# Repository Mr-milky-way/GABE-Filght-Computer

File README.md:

# G.A.B.E.-Filght-Computer
*Good Avionics, Bad Engineer*

## What is it?
The GABE flight computer is an open source rocket flight computer for controlling amateur or model rockets. It's a 4 layer PCB and pretty standard. It has a CoCom locked GPS, and 2 IMUs, a BMP390, 8 different servo header pins and can be powered off of a 12-26v battery. It uses and arm switch to power it on and has 6 pyro channels. It uses the MIMXRT1062DVJ6B with a teensy bootloader.

I tried to make it look nice but IDK, also that cad needs some work so thats why it's not shown.

> [!NOTE]
> The code is a demo of the Servos, LED, Pyros, and buzzer. This is so I have A low or very low ITAR risk. :)

## Why?
For aboout 3 years at this point I have wanted to make a Fin controlled rocket, and my first flight computter was, well a first. It didn't work really well and ended up frying itself via the servo PWM lines (I fixed that on this one with a level shifter). It was also large and bulky and the wire connectors were to small, not to mention it was ugly. So I set out to make this one.
I wanted it to look nice and work well and use mostly SMD parts, and for the most part I did.

## PICTURES

## BOM
Some parts have a value different from what it should be, this is because it was only one I could find. :)

| Part                             | Cost (all parts) | Count | Supplyer | Link                                                                                                                                                                                                                                                                          | Part ID                                     | Use              | Value         |
| -------------------------------- | ---------------- | ----- | -------- | ----------------------------------------------------------------------------------------------------------------------------------------------------------------------------------------------------------------------------------------------------------------------------- | ------------------------------------------- | ---------------- | ------------- |
| MIMXRT1062DVJ6B                  | $11.93           | 1     | Digikey  | [MIMXRT1062DVJ6B NXP USA Inc. \| Integrated Circuits (ICs) \| DigiKey](https://www.digikey.com/en/products/detail/nxp-usa-inc/MIMXRT1062DVJ6B/13574426)                                                                                                                       | U5                                          | MPU              |               |
| BNO055                           | $12.34           | 1     | Digikey  | [BNO055 Bosch Sensortec \| Sensors, Transducers \| DigiKey](https://www.digikey.com/en/products/detail/bosch-sensortec/BNO055/6136301)                                                                                                                                        | U1                                          | IMU              |               |
| TXB0108PWRG4                     | $1.41            | 1     | Digikey  | [TXB0108PWRG4 Texas Instruments \| Integrated Circuits (ICs) \| DigiKey](https://www.digikey.com/en/products/detail/texas-instruments/TXB0108PWRG4/1910158)                                                                                                                   | U6                                          | Level Shifter    |               |
| RTAN0805BKE10K0                  | $0.34            | 1     | Digikey  | [RTAN0805BKE10K0 Stackpole Electronics Inc \| Resistors \| DigiKey](https://www.digikey.com/en/products/detail/stackpole-electronics-inc/RTAN0805BKE10K0/6602188)                                                                                                             | R1                                          | Resistor         | 10KΩ          |
| FC-135R 32.7680KF-A0             | $2.13            | 3     | Digikey  | [FC-135R 32.7680KF-A0 EPSON \| Crystals, Oscillators, Resonators \| DigiKey](https://www.digikey.com/en/products/detail/epson/FC-135R-32-7680KF-A0/5604247)                                                                                                                   | X1,X2,X4                                    | Crystal          | 32.7680KHZ    |
| CHV0805N250220FCT                | $2.12            | 4     | Digikey  | [CHV0805N250220FCT Cal-Chip Electronics, Inc. \| Capacitors \| DigiKey](https://www.digikey.com/en/products/detail/cal-chip-electronics-inc/CHV0805N250220FCT/22155267)                                                                                                       | C1,C2,C5,C6                                 | Capacitor        | 22PF          |
| CC0805KRX7R9BB104                | $0.48            | 6     | Digikey  | [CC0805KRX7R9BB104 YAGEO \| Capacitors \| DigiKey](https://www.digikey.com/en/products/detail/yageo/CC0805KRX7R9BB104/302874)                                                                                                                                                 | C3,C4,C7,C8,C11,C12                         | Capacitor        | 0.1UF         |
| BNO085                           | $13.05           | 1     | Digikey  | [BNO085 CEVA Technologies, Inc. \| Sensors, Transducers \| DigiKey](https://www.digikey.com/en/products/detail/ceva-technologies-inc/BNO085/9445940)                                                                                                                          | U2                                          | IMU              |               |
| BMP390                           | $3.15            | 1     | Digikey  | [BMP390 Bosch Sensortec \| Sensors, Transducers \| DigiKey](https://www.digikey.com/en/products/detail/bosch-sensortec/BMP390/16164575)                                                                                                                                       | U3                                          |                  |               |
| NEO-M9N-00B                      | $27.00           | 1     | Digikey  | [NEO-M9N-00B u-blox \| RF and Wireless \| DigiKey](https://www.digikey.com/en/products/detail/u-blox/NEO-M9N-00B/12149174)                                                                                                                                                    | U4                                          | GPS              |               |
| CONSMA001-C-G                    | $2.79            | 1     | Digikey  | [CONSMA001-C-G TE Connectivity Linx \| Connectors, Interconnects \| DigiKey](https://www.digikey.com/en/products/detail/te-connectivity-linx/CONSMA001-C-G/11482824)                                                                                                          | X3                                          | SMA connector    |               |
| RG0603R-330-D-T10                | $0.16            | 1     | Digikey  | [RG0603R-330-D-T10 Susumu \| Resistors \| DigiKey](https://www.digikey.com/en/products/detail/susumu/RG0603R-330-D-T10/18103232)                                                                                                                                              | R2                                          | Resistor         | 33Ω           |
| BLM15PX121SN1D                   | $0.30            | 3     | Digikey  | [BLM15PX121SN1D Murata Electronics \| Filters \| DigiKey](https://www.digikey.com/en/products/detail/murata-electronics/BLM15PX121SN1D/4421095)                                                                                                                               | FB1-FB3                                     | Ferrite Bead     | 120Ω          |
| CC0805JRNPO9BN470                | $0.10            | 1     | Digikey  | [CC0805JRNPO9BN470 YAGEO \| Capacitors \| DigiKey](https://www.digikey.com/en/products/detail/yageo/CC0805JRNPO9BN470/302841)                                                                                                                                                 | C9                                          | Capacitor        | 47PF          |
| ML414H IV01E                     | $1.84            | 1     | Digikey  | [ML414H IV01E Seiko Instruments \| Battery Products \| DigiKey](https://www.digikey.com/en/products/detail/seiko-instruments/ML414H-IV01E/1889203)                                                                                                                            | BT1                                         | Battery Holder   |               |
| PMEG4005AEA-QX                   | $0.32            | 1     | Digikey  | [https://www.digikey.com/en/products/detail/nexperia-usa-inc/PMEG4005AEA-QX/17295512](https://www.digikey.com/en/products/detail/nexperia-usa-inc/PMEG4005AEA-QX/17295512)                                                                                                    | D1                                          | Diode            |               |
| RG0603P-102-B-T10                | $0.20            | 1     | Digikey  | [RG0603P-102-B-T10 Susumu \| Resistors \| DigiKey](https://www.digikey.com/en/products/detail/susumu/RG0603P-102-B-T10/18103206)                                                                                                                                              | R3                                          | Resistor         | 1KΩ           |
| C0805C105K9RACTU                 | $0.15            | 1     | Digikey  | [C0805C105K9RACTU KEMET \| Capacitors \| DigiKey](https://www.digikey.com/en/products/detail/kemet/C0805C105K9RACTU/2211772)                                                                                                                                                  | C10                                         | Capacitor        | 1UF           |
| BL-HBXJXGX32L                    | $0.50            | 1     | Digikey  | [BL-HBXJXGX32L American Bright Optoelectronics Corporation](https://www.digikey.com/en/products/detail/american-bright-optoelectronics-corporation/BL-HBXJXGX32L/9678124)                                                                                                     | D2                                          | LED              |               |
| XRCGB24M000F3M00R0               | $0.30            | 1     | Digikey  | [XRCGB24M000F3M00R0 Murata Electronics \| Crystals, Oscillators, Resonators \| DigiKey](https://www.digikey.com/en/products/detail/murata-electronics/XRCGB24M000F3M00R0/2368376) | Y1                                          | Crystal          | 24MHZ         |
| MLZ2012N4R7LT000                 | $0.10            | 1     | Digikey  | [MLZ2012N4R7LT000 TDK Corporation \| Inductors, Coils, Chokes \| DigiKey](https://www.digikey.com/en/products/detail/tdk-corporation/MLZ2012N4R7LT000/2523498)                                                                                                                | L1                                          | Inductor         | 4.7UH         |
| 112J-TDAR-R01                    | $2.52            | 1     | Digikey  | [112J-TDAR-R01 ATTEND Technology \| Connectors, Interconnects \| DigiKey](https://www.digikey.com/en/products/detail/attend-technology/112J-TDAR-R01/17633874)                                                                                                                | K1                                          | SD card holder   |               |
| BAT54CTB6_R1_00001               | $0.25            | 1     | Digikey  | [BAT54CTB6_R1_00001 Panjit International Inc. \| Discrete Semiconductor Products \| DigiKey](https://www.digikey.com/en/products/detail/panjit-international-inc/BAT54CTB6-R1-00001/15796775)                                                                                 | U$1                                         | Diode            |               |
| SKRPACE010                       | $0.21            | 1     | Digikey  | [SKRPACE010 Alps Alpine \| Switches \| DigiKey](https://www.digikey.com/en/products/detail/alps-alpine/SKRPACE010/18115579)                                                                                                                                                   | S1                                          | Switch           |               |
| W25Q64JVXGIM                     | $1.20            | 1     | PJRC     | [Bootloader Chip for DIY Teensy 4.0 & 4.1 Projects](https://www.pjrc.com/store/ic_mkl02_t4.html)                                                                                                                                                                              | U9                                          | Flash Chip       |               |
| MKL02Z32                         | $6.25            | 1     | PJRC     | [Bootloader Chip for DIY Teensy 4.0 & 4.1 Projects](https://www.pjrc.com/store/ic_mkl02_t4.html)                                                                                                                                                                              | U8                                          | Bootloader       |               |
| W25N01GVZEIG TR                  | $3.01            | 1     | Digikey  | [W25N01GVZEIG TR Winbond Electronics \| Integrated Circuits (ICs) \| DigiKey](https://www.digikey.com/en/products/detail/winbond-electronics/W25N01GVZEIG-TR/5803931)                                                                                                         | U10                                         | Flash Chip       |               |
| SMTB-1240-S-R                    | $1.35            | 1     | Digikey  | [SMTB-1240-S-R PUI Audio, Inc. \| Audio Products \| DigiKey](https://www.digikey.com/en/products/detail/pui-audio-inc/SMTB-1240-S-R/13165906)                                                                                                                                 | LS1                                         | Buzzer           |               |
| IRLML6344TRPBF                   | $2.10            | 6     | Digikey  | [IRLML6344TRPBF Infineon Technologies \| Discrete Semiconductor Products \| DigiKey](https://www.digikey.com/en/products/detail/infineon-technologies/IRLML6344TRPBF/2538152)                                                                                                 | Q2-Q7                                       | Mosfet           |               |
| LM7805MPX/NOPB                   | $1.38            | 1     | Digikey  | [LM7805MPX/NOPB Texas Instruments \| Integrated Circuits (ICs) \| DigiKey](https://www.digikey.com/en/products/detail/texas-instruments/LM7805MPX-NOPB/6110583)                                                                                                               | VR1                                         | Voltage Reguator |               |
| TLV75533PDBVR                    | $0.32            | 1     | Digikey  | [TLV75533PDBVR Texas Instruments \| Integrated Circuits (ICs) \| DigiKey](https://www.digikey.com/en/products/detail/texas-instruments/TLV75533PDBVR/9356541)                                                                                                                 | U7                                          | Voltage Reguator |               |
| AK100/2DS-5.0-V-GREY             | $5.64            | 12    | Digikey  | [https://www.digikey.com/en/products/detail/ptr-hartmann/AK100-2DS-5-0-V-GREY/24787150](https://www.digikey.com/en/products/detail/ptr-hartmann/AK100-2DS-5-0-V-GREY/24787150)                                                                                                | U$2-U$13                                    | Terminal Block   |               |
| GCJ21BL8YA224KA01L               | $3.52            | 11    | Digikey  | [GCJ21BL8YA224KA01L Murata Electronics \| Capacitors \| DigiKey](https://www.digikey.com/en/products/detail/murata-electronics/GCJ21BL8YA224KA01L/11618469)                                                                                                                   | C13,C14,C17,C18,C20,C23,C26,C31,C33,C34,C36 | Capacitor        | .22UF         |
| C0805C200J3HACAUTO               | $0.26            | 2     | Digikey  | [C0805C200J3HACAUTO KEMET \| Capacitors \| DigiKey](https://www.digikey.com/en/products/detail/kemet/C0805C200J3HACAUTO/7958823)                                                                                                                                              | C15,C16                                     | Capacitor        | 20PF          |
| GRM21BR61H475KE51L               | $0.95            | 5     | Digikey  | [GRM21BR61H475KE51L Murata Electronics \| Capacitors \| DigiKey](https://www.digikey.com/en/products/detail/murata-electronics/GRM21BR61H475KE51L/4905540)                                                                                                                    | C19,C21,C24,C27,C30                         | Capacitor        | 4.7UF         |
| CGA4J1X7R1V225K125AC             | $0.46            | 1     | Digikey  | [CGA4J1X7R1V225K125AC TDK Corporation \| Capacitors \| DigiKey](https://www.digikey.com/en/products/detail/tdk-corporation/CGA4J1X7R1V225K125AC/2672856)                                                                                                                      | C25                                         | Capacitor        | 2.2UF         |
| CC0805KRX7R8BB103                | $0.10            | 1     | Digikey  | [CC0805KRX7R8BB103 YAGEO \| Capacitors \| DigiKey](https://www.digikey.com/en/products/detail/yageo/CC0805KRX7R8BB103/5884212)                                                                                                                                                | C22                                         | Capacitor        | 10NF          |
| GRM21BR6YA106KE43L               | $1.36            | 4     | Digikey  | [GRM21BR6YA106KE43L Murata Electronics \| Capacitors \| DigiKey](https://www.digikey.com/en/products/detail/murata-electronics/GRM21BR6YA106KE43L/5027598)                                                                                                                    | C28,C29,C32,C35                             | Capacitor        | 10UF          |
| C0805C120J3GACTU                 | $0.44            | 2     | Digikey  | [C0805C120J3GACTU KEMET \| Capacitors \| DigiKey](https://www.digikey.com/en/products/detail/kemet/C0805C120J3GACTU/7388391)                                                                                                                                                  | C37,C38                                     | Capacitor        | 12pF          |
| UJ2-MIBH-G-SMT-TR                | $0.44            | 1     | Digikey  | [UJ2-MIBH-G-SMT-TR Same Sky (Formerly CUI Devices) \| Connectors, Interconnects \| DigiKey](https://www.digikey.com/en/products/detail/same-sky-formerly-cui-devices/UJ2-MIBH-G-SMT-TR/13680627)                                                                              | J1                                          | USB Con          |               |
| B4B-XH-A                         | $0.17            | 1     | Digikey  | [B4B-XH-A JST Sales America Inc. \| Connectors, Interconnects \| DigiKey](https://www.digikey.com/en/products/detail/jst-sales-america-inc/B4B-XH-A/1651047)                                                                                                                  | J2                                          | JST Con          |               |
| 61300311121                      | $0.96            | 8     | Digikey  | https://www.digikey.com/en/products/detail/würth-elektronik/61300311121/4846825                                                                                                                                                                                               | M1-M8                                       | Header pins      |               |
| DMG2305UX-7                      | $0.18            | 1     | Digikey  | [DMG2305UX-7 Diodes Incorporated \| Discrete Semiconductor Products \| DigiKey](https://www.digikey.com/en/products/detail/diodes-incorporated/DMG2305UX-7/4340667)                                                                                                           | Q1                                          | Mosfet           |               |
| SDR10EZPF2201                    | $0.44            | 2     | Digikey  | [SDR10EZPF2201 Rohm Semiconductor \| Resistors \| DigiKey](https://www.digikey.com/en/products/detail/rohm-semiconductor/SDR10EZPF2201/16179905)                                                                                                                              | R4,R5                                       | Resistor         | 2.2kΩ         |
| SDR10EZPF1003                    | $0.44            | 2     | Digikey  | [SDR10EZPF1003 Rohm Semiconductor \| Resistors \| DigiKey](https://www.digikey.com/en/products/detail/rohm-semiconductor/SDR10EZPF1003/17140208)                                                                                                                              | R6,R7                                       | Resistor         | 100kΩ         |
| SDR10EZPF2204                    | $0.22            | 1     | Digikey  | [SDR10EZPF2204 Rohm Semiconductor \| Resistors \| DigiKey](https://www.digikey.com/en/products/detail/rohm-semiconductor/SDR10EZPF2204/19531048)                                                                                                                              | R8                                          | Resistor         | 2.2MΩ         |
| SDR10EZPF1R00                    | $1.54            | 7     | Digikey  | [SDR10EZPF1R00 Rohm Semiconductor \| Resistors \| DigiKey](https://www.digikey.com/en/products/detail/rohm-semiconductor/SDR10EZPF1R00/16179859)                                                                                                                              | R9,R13,R15,R17,R19,R21,R23                  | Resistor         | 1Ω            |
| RLT1220-F-5R00-FNH               | $0.47            | 1     | Digikey  | [RLT1220-F-5R00-FNH Delta Electronics/Cyntec \| Resistors \| DigiKey](https://www.digikey.com/en/products/detail/delta-electronics-cyntec/RLT1220-F-5R00-FNH/9762198)                                                                                                         | R10                                         | Resistor         | 5Ω            |
| RK73H2ATTD64R9F                  | $0.10            | 1     | Digikey  | [RK73H2ATTD64R9F KOA Speer Electronics, Inc. \| Resistors \| DigiKey](https://www.digikey.com/en/products/detail/koa-speer-electronics-inc/RK73H2ATTD64R9F/10228485?)                                                                                                         | R11                                         | Resistor         | 65Ω (64.9)    |
| SDR10EZPF4700                    | $1.32            | 6     | Digikey  | [SDR10EZPF4700 Rohm Semiconductor \| Resistors \| DigiKey](https://www.digikey.com/en/products/detail/rohm-semiconductor/SDR10EZPF4700/17140152)                                                                                                                              | R12,R14,R16,R18,R20,R22                     | Resistor         | 470Ω          |
| RT0805BRD07723RL                 | $0.17            | 1     | Digikey  | [RT0805BRD07723RL YAGEO \| Resistors \| DigiKey](https://www.digikey.com/en/products/detail/yageo/RT0805BRD07723RL/7708570)                                                                                                                                                   | R24                                         | Resistor         | 722Ω (723)    |
| RK73H2ATTD1691F                  | $0.10            | 1     | Digikey  | [RK73H2ATTD1691F KOA Speer Electronics, Inc. \| Resistors \| DigiKey](https://www.digikey.com/en/products/detail/koa-speer-electronics-inc/RK73H2ATTD1691F/10234184)                                                                                                          | R25                                         | Resistor         | 1700Ω (1.69k) |
| COST OF MAIN PCB AND SMD-Stencil | $81.42           | 1     | PCB Way  |                                                                                                                                                                                                                                                                               |                                             | PCB              |               |
| TOTAL                            | $200.00          | 120   |          |                                                                                                                                                                                                                                                                               |                                             |                  |               |

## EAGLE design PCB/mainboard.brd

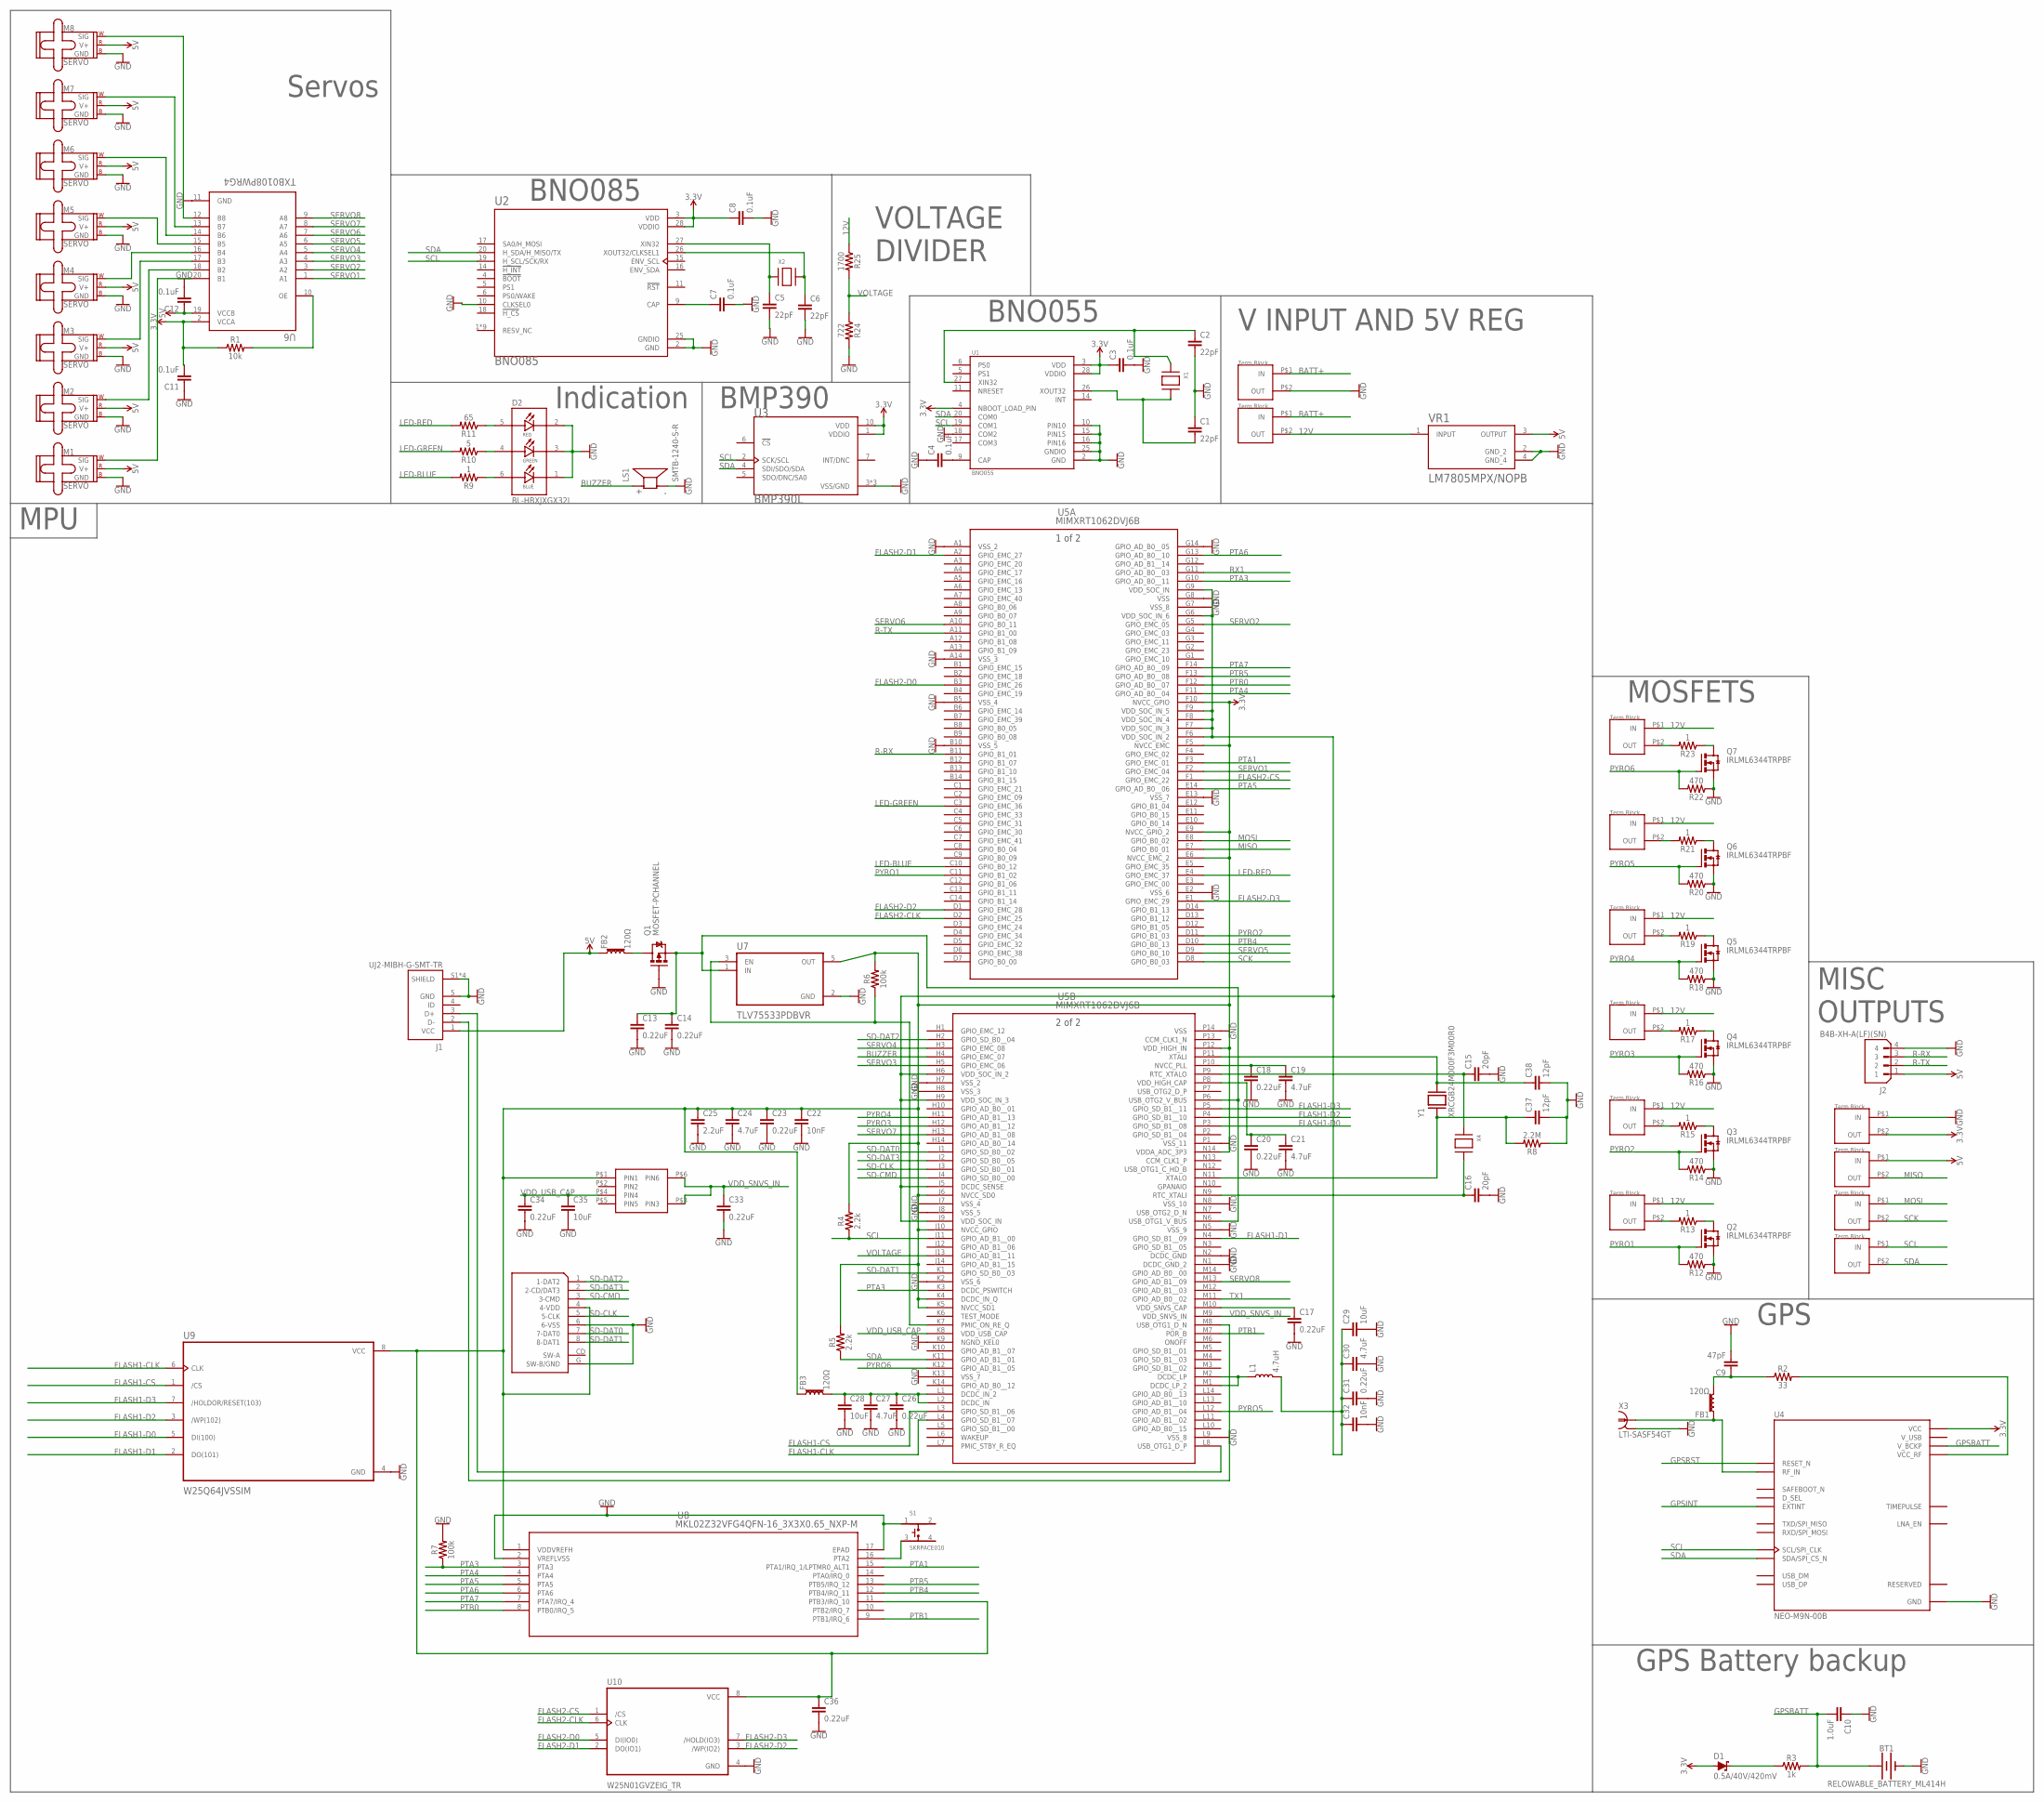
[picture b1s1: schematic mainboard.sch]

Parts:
BT1: RELOWABLE_BATTERY_ML414H; ML414H_IV01E
C1, C2, C5, C6: 22pF; 0805
C3, C4, C7, C8, C11, C12: 0.1uF; 0805
C9: 47pF; 0805
C10: 1.0uF; 0805
C13, C14, C17, C18, C20, C23, C26, C31, C33, C34, C36: 0.22uF; 0805
C15, C16: 20pF; 0805
C19, C21, C24, C27, C30: 4.7uF; 0805
C22, C32: 10nF; 0805
C25: 2.2uF; 0805
C28, C29, C35: 10uF; 0805
C37, C38: 12pF; 0805
D1: 0.5A/40V/420mV; SOD-323
D2: BL-HBXJXGX32L; LED_BL-HBXJXGX32L
FB1, FB2, FB3: 120Ω; 0805
J1: UJ2-MIBH-G-SMT-TR; CUI_UJ2-MIBH-G-SMT-TR
J2: B4B-XH-A(LF)(SN); JST_B4B-XH-A(LF)(SN)
K1: 112J-TDAR-R01
L1: 4.7uH; 0805-WIDE
LS1: SMTB-1240-S-R; XDCR_SMTB-1240-S-R
M1, M2, M3, M4, M5, M6, M7, M8: SERVO; 1X03
Q1: MOSFET-PCHANNEL; SOT23-3
Q2, Q3, Q4, Q5, Q6, Q7: IRLML6344TRPBF; SOT23
R1: 10k; 0805
R2: 33; 0805
R3: 1k; 0805
R4, R5: 2.2k; 0805
R6, R7: 100k; 0805
R8: 2.2M; 0805
R9, R13, R15, R17, R19, R21, R23: 1; 0805
R10: 5; 0805
R11: 65; 0805
R12, R14, R16, R18, R20, R22: 470; 0805
R24: 722; 0805
R25: 1700; 0805
S1: SKRPACE010; SW_SKRPACE010
U1: BNO055; LGA28R50P4X10_380X520X100
U2: BNO085; IC_BNO085
U3: BMP390L; XDCR_BMP390L
U4: NEO-M9N-00B; XCVR_NEO-M9N-00B
U5: MIMXRT1062DVJ6B; BGA196_MIMXRT_NXP
U6: TXB0108PWRG4; SOP65P640X120-20N
U7: TLV75533PDBVR; SOT95P280X145-5N
U8: MKL02Z32VFG4QFN-16_3X3X0.65_NXP-M; QFN-16_3X3X0.65_NXP-M
U9: W25Q64JVSSIM; SOIC127P790X216-8N
U10: W25N01GVZEIG_TR; SON127P800X600X80-9N
U$1: BAT54CTB6
U$2, U$3, U$4, U$5, U$6, U$7, U$8, U$9, U$10, U$11, U$12, U$13: AK100
VR1: LM7805MPX/NOPB; VREG_LM7805MPX/NOPB
X1, X2, X4: XTAL-3.2X1.5; XTAL3215
X3: LTI-SASF54GT
Y1: XRCGB24M000F3M00R0; OSC_XRCGB24M000F3M00R0

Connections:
3.3V: C3.1, C8.1, C11.2, C22.1, C23.1, C24.1, C25.1, C36.1, D1.A, FB3.1, K1.4 (4-VDD), R1.1, R4.2, R5.2, R6.2, U1.3 (VDD), U1.4 (NBOOT_LOAD_PIN), U1.28 (VDDIO), U2.3 (VDD), U2.28 (VDDIO), U3.1 (VDDIO), U3.10 (VDD), U4.23 (VCC), U5.E6 (NVCC_EMC_2), U5.E9 (NVCC_GPIO_2), U5.F5 (NVCC_EMC), U5.F10 (NVCC_GPIO), U5.J6 (NVCC_SD0), U5.J10 (NVCC_GPIO), U5.K4 (DCDC_IN_Q), U5.K5 (NVCC_SD1), U5.N14 (VDDA_ADC_3P3), U5.P12 (VDD_HIGH_IN), U6.2 (VCCA), U7.5 (OUT), U8.1 (VDDVREFH), U8.11 (PTB3/IRQ_10), U9.8 (VCC), U10.8 (VCC), U$1.P$1 (PIN1), U$11.P$2 (OUT)
5V: C12.1, FB2.1, J1.1 (VCC), J2.1, M1.2 (V+), M2.2 (V+), M3.2 (V+), M4.2 (V+), M5.2 (V+), M6.2 (V+), M7.2 (V+), M8.2 (V+), U6.19 (VCCB), U$10.P$1 (IN), VR1.3 (OUTPUT)
12V: R25.1, U$2.P$1 (IN), U$3.P$1 (IN), U$4.P$1 (IN), U$5.P$1 (IN), U$6.P$1 (IN), U$8.P$1 (IN), U$13.P$2 (OUT), VR1.1 (INPUT)
BATT+: U$12.P$1 (IN), U$13.P$1 (IN)
BUZZER: LS1.P (+), U5.H4 (GPIO_EMC_07)
FLASH1-CLK: U5.L4 (GPIO_SD_B1__07), U9.6 (CLK)
FLASH1-CS: U5.L3 (GPIO_SD_B1__06), U9.1 (/CS)
FLASH1-D0: U5.P3 (GPIO_SD_B1__08), U9.5 (DI(100))
FLASH1-D1: U5.N4 (GPIO_SD_B1__09), U9.2 (DO(101))
FLASH1-D2: U5.P4 (GPIO_SD_B1__10), U9.3 (/WP(102))
FLASH1-D3: U5.P5 (GPIO_SD_B1__11), U9.7 (/HOLDOR/RESET(103))
FLASH2-CLK: U5.D2 (GPIO_EMC_25), U10.6 (CLK)
FLASH2-CS: U5.F1 (GPIO_EMC_22), U10.1 (/CS)
FLASH2-D0: U5.B3 (GPIO_EMC_26), U10.5 (DI(IO0))
FLASH2-D1: U5.A2 (GPIO_EMC_27), U10.2 (DO(IO1))
FLASH2-D2: U5.D1 (GPIO_EMC_28), U10.3 (/WP(IO2))
FLASH2-D3: U5.E1 (GPIO_EMC_29), U10.7 (/HOLD(IO3))
GND: BT1.-, C1.1, C2.2, C3.2, C4.1, C5.2, C6.2, C7.2, C8.2, C9.2, C10.1, C11.1, C12.2, C13.2, C14.2, C15.2, C16.2, C17.2, C18.2, C19.2, C20.2, C21.2, C22.2, C23.2, C24.2, C25.2, C26.2, C27.2, C28.2, C29.2, C30.2, C31.2, C32.2, C33.2, C34.2, C35.2, C36.2, C37.2, C38.2, D2.1 (B_C), D2.2 (R_C), D2.3 (G_C), J1.5 (GND), J1.S1 (SHIELD), J1.S2 (SHIELD), J1.S3 (SHIELD), J1.S4 (SHIELD), J2.4, K1.6 (6-VSS), K1.G (SW-B/GND), LS1.N (-), M1.3 (GND), M2.3 (GND), M3.3 (GND), M4.3 (GND), M5.3 (GND), M6.3 (GND), M7.3 (GND), M8.3 (GND), Q1.1 (G), Q2.2 (S), Q3.2 (S), Q4.2 (S), Q5.2 (S), Q6.2 (S), Q7.2 (S), R7.2, R8.1, R12.1, R14.1, R16.1, R18.1, R20.1, R22.1, R24.2, S1.1, U1.2 (GND), U1.10 (PIN10), U1.15 (PIN15), U1.16 (PIN16), U1.18 (COM2), U1.25 (GNDIO), U2.2 (GND), U2.10 (CLKSEL0), U2.25 (GNDIO), U3.3 (VSS/GND), U3.8 (VSS/GND), U3.9 (VSS/GND), U4.10 (GND), U4.12 (GND), U4.13 (GND), U4.24 (GND), U5.A1 (VSS_2), U5.A14 (VSS_3), U5.B5 (VSS_4), U5.B10 (VSS_5), U5.E2 (VSS_6), U5.E13 (VSS_7), U5.G7 (VSS_8), U5.G8 (VSS), U5.G14 (GPIO_AD_B0__05), U5.H7 (VSS_2), U5.H8 (VSS_3), U5.J7 (VSS_4), U5.J8 (VSS_5), U5.K2 (VSS_6), U5.K9 (NGND_KEL0), U5.K13 (VSS_7), U5.L9 (VSS_8), U5.N1 (DCDC_GND_2), U5.N2 (DCDC_GND), U5.N5 (VSS_9), U5.N8 (VSS_10), U5.P1 (VSS_11), U5.P14 (VSS), U6.11 (GND), U7.2 (GND), U8.2 (VREFLVSS), U8.17 (EPAD), U9.4 (GND), U10.4 (GND), U$11.P$1 (IN), U$12.P$2 (OUT), VR1.2 (GND_2), VR1.4 (GND_4), X3.2, X3.3 (2), X3.4 (2), X3.5 (2)
GPIO_AD_B0__01: U5.H10 (GPIO_AD_B0__01)
GPIO_B1_05: U5.D12 (GPIO_B1_05)
GPIO_B1_14: U5.C14 (GPIO_B1_14)
GPIO_EMC_24: U5.D3 (GPIO_EMC_24)
GPSBATT: BT1.+, C10.2, R3.2, U4.22 (V_BCKP)
GPSINT: U4.4 (EXTINT)
GPSRST: U4.8 (RESET_N)
LED-BLUE: R9.2, U5.C10 (GPIO_B0_12)
LED-GREEN: R10.2, U5.C3 (GPIO_EMC_36)
LED-RED: R11.2, U5.E4 (GPIO_EMC_37)
MISO: U5.E7 (GPIO_B0_01), U$10.P$2 (OUT)
MOSI: U5.E8 (GPIO_B0_02), U$9.P$1 (IN)
unnamed: C2.1, U1.27 (XIN32), X1.P$1
unnamed: C1.2, U1.26 (XOUT32), X1.P$2
unnamed: C4.2, U1.9 (CAP)
unnamed: C5.1, U2.27 (XIN32), X2.P$1
unnamed: C6.1, U2.26 (XOUT32/CLKSEL1), X2.P$2
unnamed: C7.1, U2.9 (CAP)
unnamed: FB1.1, U4.11 (RF_IN), X3.1
unnamed: R2.2, U4.9 (VCC_RF)
unnamed: C9.1, FB1.2, R2.1
unnamed: D1.C, R3.1
unnamed: C16.1, U5.N9 (RTC_XTALI), X4.P$2
unnamed: R6.1, U5.K7 (PMIC_ON_RE_Q), U7.3 (EN)
unnamed: M8.1 (SIG), U6.12 (B8)
unnamed: M7.1 (SIG), U6.13 (B7)
unnamed: M6.1 (SIG), U6.14 (B6)
unnamed: M5.1 (SIG), U6.15 (B5)
unnamed: M1.1 (SIG), U6.20 (B1)
unnamed: M2.1 (SIG), U6.18 (B2)
unnamed: M3.1 (SIG), U6.17 (B3)
unnamed: M4.1 (SIG), U6.16 (B4)
unnamed: R1.2, U6.10 (OE)
unnamed: J1.2 (D-), U5.M8 (USB_OTG1_D_N)
unnamed: J1.3 (D+), U5.L8 (USB_OTG1_D_P)
unnamed: FB2.2, Q1.3 (D)
unnamed: C15.1, U5.P9 (RTC_XTALO), X4.P$1
unnamed: C13.1, C14.1, Q1.2 (S), U5.N6 (USB_OTG1_V_BUS), U5.P6 (USB_OTG2_V_BUS), U7.1 (IN)
unnamed: C26.1, C27.1, C28.1, FB3.2, U5.L1 (DCDC_IN_2), U5.L2 (DCDC_IN)
unnamed: L1.1, U5.M1 (DCDC_LP_2), U5.M2 (DCDC_LP)
unnamed: C29.1, C30.1, C31.1, C32.1, L1.2, U5.F6 (VDD_SOC_IN_2), U5.F7 (VDD_SOC_IN_3), U5.F8 (VDD_SOC_IN_4), U5.F9 (VDD_SOC_IN_5), U5.G6 (VDD_SOC_IN_6), U5.G9 (VDD_SOC_IN), U5.H6 (VDD_SOC_IN_2), U5.H9 (VDD_SOC_IN_3), U5.J5 (DCDC_SENSE), U5.J9 (VDD_SOC_IN)
unnamed: C17.1, U5.M10 (VDD_SNVS_CAP)
unnamed: C20.1, C21.1, U5.P8 (VDD_HIGH_CAP)
unnamed: C18.1, C19.1, U5.P10 (NVCC_PLL)
unnamed: S1.3, U8.16 (PTA2)
unnamed: C37.1, R8.2, U5.N11 (XTALO), Y1.1
unnamed: C38.1, U5.P11 (XTALI), Y1.3
unnamed: D2.6 (B_A), R9.1
unnamed: D2.4 (G_A), R10.1
unnamed: D2.5 (R_A), R11.1
unnamed: Q2.3 (D), R13.1
unnamed: R13.2, U$8.P$2 (OUT)
unnamed: Q3.3 (D), R15.1
unnamed: R15.2, U$2.P$2 (OUT)
unnamed: Q4.3 (D), R17.1
unnamed: R17.2, U$3.P$2 (OUT)
unnamed: Q5.3 (D), R19.1
unnamed: R19.2, U$4.P$2 (OUT)
unnamed: Q6.3 (D), R21.1
unnamed: R21.2, U$5.P$2 (OUT)
unnamed: Q7.3 (D), R23.1
unnamed: R23.2, U$6.P$2 (OUT)
PTA1: U5.F3 (GPIO_EMC_01), U8.15 (PTA1/IRQ_1/LPTMR0_ALT1)
PTA3: R7.1, U5.G10 (GPIO_AD_B0__11), U5.K3 (DCDC_PSWITCH), U8.3 (PTA3)
PTA4: U5.F11 (GPIO_AD_B0__04), U8.4 (PTA4)
PTA5: U5.E14 (GPIO_AD_B0__06), U8.5 (PTA5)
PTA6: U5.G13 (GPIO_AD_B0__10), U8.6 (PTA6)
PTA7: U5.F14 (GPIO_AD_B0__09), U8.7 (PTA7/IRQ_4)
PTB0: U5.F12 (GPIO_AD_B0__07), U8.8 (PTB0/IRQ_5)
PTB1: U5.M7 (POR_B), U8.9 (PTB1/IRQ_6)
PTB4: U5.D10 (GPIO_B0_13), U8.12 (PTB4/IRQ_11)
PTB5: U5.F13 (GPIO_AD_B0__08), U8.13 (PTB5/IRQ_12)
PYRO1: Q2.1 (G), R12.2, U5.C11 (GPIO_B1_02)
PYRO2: Q3.1 (G), R14.2, U5.D11 (GPIO_B1_03)
PYRO3: Q4.1 (G), R16.2, U5.H12 (GPIO_AD_B1__12)
PYRO4: Q5.1 (G), R18.2, U5.H11 (GPIO_AD_B1__13)
PYRO5: Q6.1 (G), R20.2, U5.L12 (GPIO_AD_B1__04)
PYRO6: Q7.1 (G), R22.2, U5.K12 (GPIO_AD_B1__05)
R-RX: J2.3, U5.B11 (GPIO_B1_01)
R-TX: J2.2, U5.A11 (GPIO_B1_00)
RX1: U5.G11 (GPIO_AD_B0__03)
SCK: U5.D8 (GPIO_B0_03), U$9.P$2 (OUT)
SCL: R4.1, U1.19 (COM1), U2.19 (H_SCL/SCK/RX), U3.2 (SCK/SCL), U4.19 (SCL/SPI_CLK), U5.J11 (GPIO_AD_B1__00), U$7.P$1 (IN)
SD-CLK: K1.5 (5-CLK), U5.J3 (GPIO_SD_B0__01)
SD-CMD: K1.3 (3-CMD), U5.J4 (GPIO_SD_B0__00)
SD-DAT0: K1.7 (7-DAT0), U5.J1 (GPIO_SD_B0__02)
SD-DAT1: K1.8 (8-DAT1), U5.K1 (GPIO_SD_B0__03)
SD-DAT2: K1.1 (1-DAT2), U5.H2 (GPIO_SD_B0__04)
SD-DAT3: K1.2 (2-CD/DAT3), U5.J2 (GPIO_SD_B0__05)
SDA: R5.1, U1.20 (COM0), U2.20 (H_SDA/H_MISO/TX), U3.4 (SDI/SDO/SDA), U4.18 (SDA/SPI_CS_N), U5.K11 (GPIO_AD_B1__01), U$7.P$2 (OUT)
SERVO1: U5.F2 (GPIO_EMC_04), U6.1 (A1)
SERVO2: U5.G5 (GPIO_EMC_05), U6.3 (A2)
SERVO3: U5.H5 (GPIO_EMC_06), U6.4 (A3)
SERVO4: U5.H3 (GPIO_EMC_08), U6.5 (A4)
SERVO5: U5.D9 (GPIO_B0_10), U6.6 (A5)
SERVO6: U5.A10 (GPIO_B0_11), U6.7 (A6)
SERVO7: U5.H13 (GPIO_AD_B1__08), U6.8 (A7)
SERVO8: U5.M13 (GPIO_AD_B1__09), U6.9 (A8)
TX1: U5.M11 (GPIO_AD_B0__02)
VDD_SNVS_IN: C33.1, U5.M9 (VDD_SNVS_IN), U$1.P$3 (PIN3), U$1.P$6 (PIN6)
VDD_USB_CAP: C34.1, C35.1, U5.K8 (VDD_USB_CAP), U$1.P$4 (PIN4)
VOLTAGE: R24.1, R25.2, U5.J13 (GPIO_AD_B1__11)
V_USB: U4.7 (V_USB)

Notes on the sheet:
Servos
GPS
GPS Battery backup
BMP390
BNO085
BNO055
MPU
Indication
MOSFETS
V INPUT AND 5V REG
MISC OUTPUTS
VOLTAGE DIVIDER

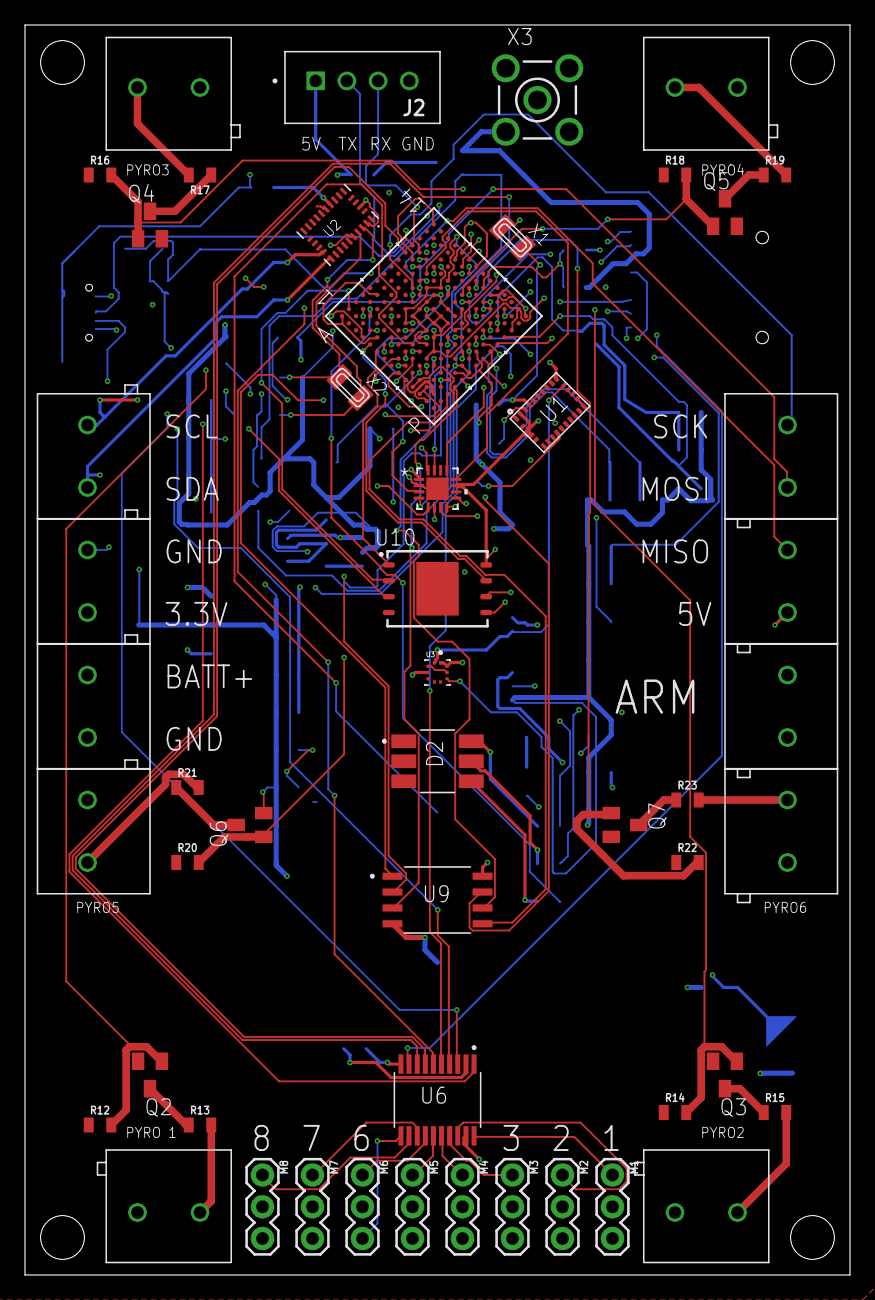
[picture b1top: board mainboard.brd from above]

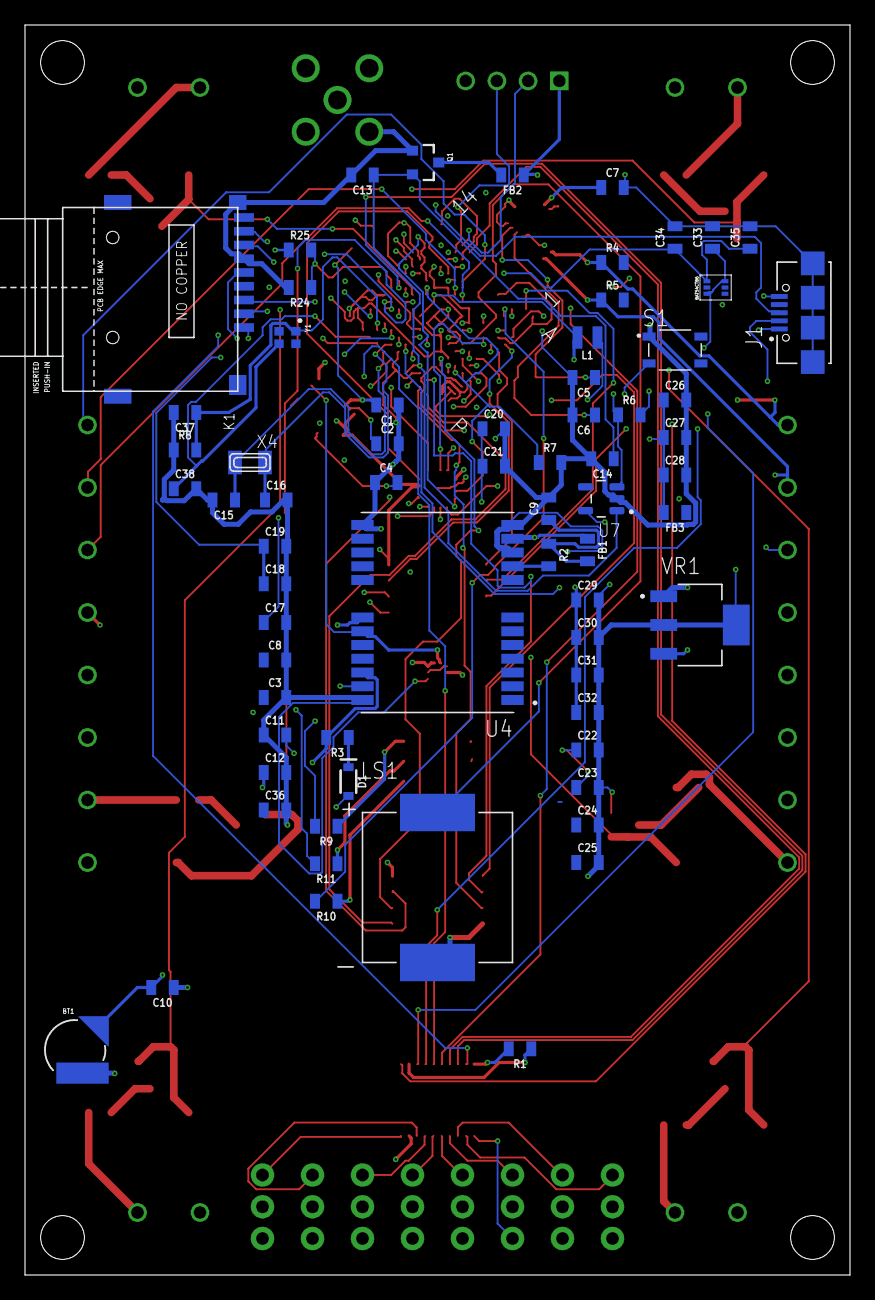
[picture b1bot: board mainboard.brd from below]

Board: 4 copper layers, 66.0 x 100.0 mm, 119 parts (68 on the bottom side), 112 nets.

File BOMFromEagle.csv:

Part,Value,Device,Package,Description
BT1,RELOWABLE_BATTERY_ML414H,RELOWABLE_BATTERY_ML414H,ML414H_IV01E,SEIKO Reflowable Lithium Batteries
C1,22pF,1.0UF-0805-25V-10%,805,ceramic capacitors
C2,22pF,1.0UF-0805-25V-10%,805,ceramic capacitors
C3,0.1uF,1.0UF-0805-25V-10%,805,ceramic capacitors
C4,0.1uF,1.0UF-0805-25V-10%,805,ceramic capacitors
C5,22pF,1.0UF-0805-25V-10%,805,ceramic capacitors
C6,22pF,1.0UF-0805-25V-10%,805,ceramic capacitors
C7,0.1uF,1.0UF-0805-25V-10%,805,ceramic capacitors
C8,0.1uF,1.0UF-0805-25V-10%,805,ceramic capacitors
C9,47pF,1.0UF-0805-25V-10%,805,ceramic capacitors
C10,1.0uF,1.0UF-0805-25V-10%,805,ceramic capacitors
C11,0.1uF,1.0UF-0805-25V-10%,805,ceramic capacitors
C12,0.1uF,1.0UF-0805-25V-10%,805,ceramic capacitors
C13,0.22uF,1.0UF-0805-25V-10%,805,ceramic capacitors
C14,0.22uF,1.0UF-0805-25V-10%,805,ceramic capacitors
C15,20pF,1.0UF-0805-25V-10%,805,ceramic capacitors
C16,20pF,1.0UF-0805-25V-10%,805,ceramic capacitors
C17,0.22uF,1.0UF-0805-25V-10%,805,ceramic capacitors
C18,0.22uF,1.0UF-0805-25V-10%,805,ceramic capacitors
C19,4.7uF,1.0UF-0805-25V-10%,805,ceramic capacitors
C20,0.22uF,1.0UF-0805-25V-10%,805,ceramic capacitors
C21,4.7uF,1.0UF-0805-25V-10%,805,ceramic capacitors
C22,10nF,1.0UF-0805-25V-10%,805,ceramic capacitors
C23,0.22uF,1.0UF-0805-25V-10%,805,ceramic capacitors
C24,4.7uF,1.0UF-0805-25V-10%,805,ceramic capacitors
C25,2.2uF,1.0UF-0805-25V-10%,805,ceramic capacitors
C26,0.22uF,1.0UF-0805-25V-10%,805,ceramic capacitors
C27,4.7uF,1.0UF-0805-25V-10%,805,ceramic capacitors
C28,10uF,1.0UF-0805-25V-10%,805,ceramic capacitors
C29,10uF,1.0UF-0805-25V-10%,805,ceramic capacitors
C30,4.7uF,1.0UF-0805-25V-10%,805,ceramic capacitors
C31,0.22uF,1.0UF-0805-25V-10%,805,ceramic capacitors
C32,10nF,1.0UF-0805-25V-10%,805,ceramic capacitors
C33,0.22uF,1.0UF-0805-25V-10%,805,ceramic capacitors
C34,0.22uF,1.0UF-0805-25V-10%,805,ceramic capacitors
C35,10uF,1.0UF-0805-25V-10%,805,ceramic capacitors
C36,0.22uF,1.0UF-0805-25V-10%,805,ceramic capacitors
C37,12pF,1.0UF-0805-25V-10%,805,ceramic capacitors
C38,12pF,1.0UF-0805-25V-10%,805,ceramic capacitors
D1,0.5A/40V/420mV,DIODE-SCHOTTKY-PMEG4005EJ,SOD-323,Schottky diode
D2,BL-HBXJXGX32L,BL-HBXJXGX32L,LED_BL-HBXJXGX32L,
FB1,120Ω,FERRITE_BEAD-0805-220Ω-100MHZ-2A,805,"Ferrite Bead (blocks, cores, rings, chokes, etc.)"
FB2,120Ω,FERRITE_BEAD-0805-220Ω-100MHZ-2A,805,"Ferrite Bead (blocks, cores, rings, chokes, etc.)"
FB3,120Ω,FERRITE_BEAD-0805-220Ω-100MHZ-2A,805,"Ferrite Bead (blocks, cores, rings, chokes, etc.)"
J1,UJ2-MIBH-G-SMT-TR,UJ2-MIBH-G-SMT-TR,CUI_UJ2-MIBH-G-SMT-TR,
J2,B4B-XH-A(LF)(SN),B4B-XH-A(LF)(SN),JST_B4B-XH-A(LF)(SN),
K1,112J-TDAR-R01,112J-TDAR-R01,112J-TDAR-R01,
L1,4.7uH,INDUCTOR-0805_WIDE-2.2UH,0805-WIDE,Inductors
LS1,SMTB-1240-S-R,SMTB-1240-S-R,XDCR_SMTB-1240-S-R,
M1,SERVO,SERVO,1X03,Servo Motor
M2,SERVO,SERVO,1X03,Servo Motor
M3,SERVO,SERVO,1X03,Servo Motor
M4,SERVO,SERVO,1X03,Servo Motor
M5,SERVO,SERVO,1X03,Servo Motor
M6,SERVO,SERVO,1X03,Servo Motor
M7,SERVO,SERVO,1X03,Servo Motor
M8,SERVO,SERVO,1X03,Servo Motor
Q1,MOSFET-PCHANNEL,MOSFET-PCHANNEL,SOT23-3,Generic PMOSFET
Q2,IRLML6344TRPBF,IRLML6344TRPBF,SOT23,
Q3,IRLML6344TRPBF,IRLML6344TRPBF,SOT23,
Q4,IRLML6344TRPBF,IRLML6344TRPBF,SOT23,
Q5,IRLML6344TRPBF,IRLML6344TRPBF,SOT23,
Q6,IRLML6344TRPBF,IRLML6344TRPBF,SOT23,
Q7,IRLML6344TRPBF,IRLML6344TRPBF,SOT23,
R1,10k,0.3OHM-0805-1/8W-1%,805,resistor
R2,33,0.3OHM-0805-1/8W-1%,805,resistor
R3,1k,0.3OHM-0805-1/8W-1%,805,resistor
R4,2.2k,0.3OHM-0805-1/8W-1%,805,resistor
R5,2.2k,0.3OHM-0805-1/8W-1%,805,resistor
R6,100k,0.3OHM-0805-1/8W-1%,805,resistor
R7,100k,0.3OHM-0805-1/8W-1%,805,resistor
R8,2.2M,0.3OHM-0805-1/8W-1%,805,resistor
R9,1,0.3OHM-0805-1/8W-1%,805,resistor
R10,5,0.3OHM-0805-1/8W-1%,805,resistor
R11,65,0.3OHM-0805-1/8W-1%,805,resistor
R12,470,0.3OHM-0805-1/8W-1%,805,resistor
R13,1,0.3OHM-0805-1/8W-1%,805,resistor
R14,470,0.3OHM-0805-1/8W-1%,805,resistor
R15,1,0.3OHM-0805-1/8W-1%,805,resistor
R16,470,0.3OHM-0805-1/8W-1%,805,resistor
R17,1,0.3OHM-0805-1/8W-1%,805,resistor
R18,470,0.3OHM-0805-1/8W-1%,805,resistor
R19,1,0.3OHM-0805-1/8W-1%,805,resistor
R20,470,0.3OHM-0805-1/8W-1%,805,resistor
R21,1,0.3OHM-0805-1/8W-1%,805,resistor
R22,470,0.3OHM-0805-1/8W-1%,805,resistor
R23,1,0.3OHM-0805-1/8W-1%,805,resistor
R24,722,0.3OHM-0805-1/8W-1%,805,resistor
R25,1700,0.3OHM-0805-1/8W-1%,805,resistor
S1,SKRPACE010,SKRPACE010,SW_SKRPACE010,
U$1,BAT54CTB6,BAT54CTB6,BAT54CTB6,
U$2,AK100,AK100,AK100,
U$3,AK100,AK100,AK100,
U$4,AK100,AK100,AK100,
U$5,AK100,AK100,AK100,
U$6,AK100,AK100,AK100,
U$7,AK100,AK100,AK100,
U$8,AK100,AK100,AK100,
U$9,AK100,AK100,AK100,
U$10,AK100,AK100,AK100,
U$11,AK100,AK100,AK100,
U$12,AK100,AK100,AK100,
U$13,AK100,AK100,AK100,
U1,BNO055,BNO055,LGA28R50P4X10_380X520X100,
U2,BNO085,BNO085,IC_BNO085,
U3,BMP390L,BMP390L,XDCR_BMP390L,
U4,NEO-M9N-00B,NEO-M9N-00B,XCVR_NEO-M9N-00B,
U5,MIMXRT1062DVJ6B,MIMXRT1062DVJ6B,BGA196_MIMXRT_NXP,
U6,TXB0108PWRG4,TXB0108PWRG4,SOP65P640X120-20N,
U7,TLV75533PDBVR,TLV75533PDBVR,SOT95P280X145-5N,
U8,MKL02Z32VFG4QFN-16_3X3X0.65_NXP-M,MKL02Z32VFG4QFN-16_3X3X0.65_NXP-M,QFN-16_3X3X0.65_NXP-M,
U9,W25Q64JVSSIM,W25Q64JVSSIM,SOIC127P790X216-8N,
U10,W25N01GVZEIG_TR,W25N01GVZEIG_TR,SON127P800X600X80-9N,
VR1,LM7805MPX/NOPB,LM7805MPX/NOPB,VREG_LM7805MPX/NOPB,
X1,,XTAL-3.2X1.5,XTAL3215,"Low cost SMT crystals, no capacitors included"
X2,,XTAL-3.2X1.5,XTAL3215,"Low cost SMT crystals, no capacitors included"
X3,LTI-SASF54GT,LTI-SASF54GT,LTI-SASF54GT,SMA vertical PCB thrue hole jack
X4,,XTAL-3.2X1.5,XTAL3215,"Low cost SMT crystals, no capacitors included"
Y1,XRCGB24M000F3M00R0,XRCGB24M000F3M00R0,OSC_XRCGB24M000F3M00R0,

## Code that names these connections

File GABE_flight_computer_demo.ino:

/* 
This is just a demo of the servos, LED, Pyros, and Buzzer.
*/

#include <PWMServo.h>

PWMServo servo1;
PWMServo servo2;
PWMServo servo3;
PWMServo servo4;
PWMServo servo5;
PWMServo servo6;
PWMServo servo7;
PWMServo servo8;


int pos = 0;
int PYRO1 = 36;
int PYRO2 = 37;
int PYRO3 = 38;
int PYRO4 = 39;
int PYRO5 = 40;
int PYRO6 = 41;
int R_LED = 30;
int B_LED = 32;
int G_LED = 31;
int buzzer = 33;

void setup() {
  Serial.begin(115200);
  Serial.write("Start up");
  pinMode(R_LED, OUTPUT);
  pinMode(B_LED, OUTPUT);
  pinMode(G_LED, OUTPUT);

  pinMode(PYRO1, OUTPUT);
  pinMode(PYRO2, OUTPUT);
  pinMode(PYRO3, OUTPUT);
  pinMode(PYRO4, OUTPUT);
  pinMode(PYRO5, OUTPUT);
  pinMode(PYRO6, OUTPUT);
  


  servo1.attach(2);
  servo2.attach(3);
  servo3.attach(4);
  servo4.attach(5);
  servo5.attach(6);
  servo6.attach(9);
  servo7.attach(22);
  servo8.attach(23);
}

void loop() {

  Serial.write("LEDs");
  digitalWrite(R_LED, LOW);
  digitalWrite(B_LED, LOW);
  digitalWrite(G_LED, LOW);
  delay(50);
  digitalWrite(R_LED, HIGH);
  digitalWrite(B_LED, LOW);
  digitalWrite(G_LED, LOW);
  delay(50);
  digitalWrite(R_LED, LOW);
  digitalWrite(B_LED, HIGH);
  digitalWrite(G_LED, LOW);
  delay(50);
  digitalWrite(R_LED, LOW);
  digitalWrite(B_LED, LOW);
  digitalWrite(G_LED, HIGH);
  delay(50);
  digitalWrite(R_LED, LOW);
  digitalWrite(B_LED, LOW);
  digitalWrite(G_LED, LOW);
  delay(50);
  digitalWrite(R_LED, HIGH);
  digitalWrite(B_LED, HIGH);
  digitalWrite(G_LED, HIGH);

  Serial.write("Servo and buzzer");
  for(pos = 0; pos < 180; pos += 1) {
    servo1.write(pos);
    servo2.write(pos);
    servo3.write(pos);
    servo4.write(pos);
    servo5.write(pos);
    servo6.write(pos);
    servo7.write(pos);
    servo8.write(pos);
    tone(buzzer, 1000);
    delay(50);
    noTone(buzzer);
  }
  for(pos = 180; pos>=1; pos-=5) {
    servo1.write(pos);
    servo2.write(pos);
    servo3.write(pos);
    servo4.write(pos);
    servo5.write(pos);
    servo6.write(pos);
    servo7.write(pos);
    servo8.write(pos);
    tone(buzzer, 1000);
    delay(50);
    noTone(buzzer);
  }
  for(pos = 0; pos < 180; pos += 10) {
    servo1.write(pos);
    servo2.write(pos);
    servo3.write(pos);
    servo4.write(pos);
    servo5.write(pos);
    servo6.write(pos);
    servo7.write(pos);
    servo8.write(pos);
    tone(buzzer, 1000);
    delay(50);
    noTone(buzzer);
  }
  for(pos = 180; pos>=1; pos-=15) {
    servo1.write(pos);
    servo2.write(pos);
    servo3.write(pos);
    servo4.write(pos);
    servo5.write(pos);
    servo6.write(pos);
    servo7.write(pos);
    servo8.write(pos);
    tone(buzzer, 1000);
    delay(50);
    noTone(buzzer);
  }

  Serial.write("Pyros");
  digitalWrite(PYRO1, LOW);
  digitalWrite(PYRO2, LOW);
  digitalWrite(PYRO3, LOW);
  digitalWrite(PYRO4, LOW);
  digitalWrite(PYRO5, LOW);
  digitalWrite(PYRO6, LOW);
  delay(1000);
  Serial.write("Pyro 1 ON");
  digitalWrite(PYRO1, HIGH);
  delay(1000);
  Serial.write("Pyro 1 OFF");
  Serial.write("Pyro 2 ON");
  digitalWrite(PYRO1, LOW);
  digitalWrite(PYRO2, HIGH);
  delay(1000);
  Serial.write("Pyro 2 OFF");
  Serial.write("Pyro 3 ON");
  digitalWrite(PYRO2, LOW);
  digitalWrite(PYRO3, HIGH);
  delay(1000);
  Serial.write("Pyro 3 OFF");
  Serial.write("Pyro 4 ON");
  digitalWrite(PYRO3, LOW);
  digitalWrite(PYRO4, HIGH);
  delay(1000);
  Serial.write("Pyro 4 OFF");
  Serial.write("Pyro 5 ON");
  digitalWrite(PYRO4, LOW);
  digitalWrite(PYRO5, HIGH);
  delay(1000);
  Serial.write("Pyro 5 OFF");
  Serial.write("Pyro 6 ON");
  digitalWrite(PYRO5, LOW);
  digitalWrite(PYRO6, HIGH);
  delay(1000);
  Serial.write("Pyro 6 OFF");
  digitalWrite(PYRO6, LOW);
}

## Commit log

2025-06-06 Update JOURNAL.md
    Fixed the time error
2025-06-21 Added board to repo and BOM
2025-06-21 Rename mainboard_2025-06-20.zip to Gerber.zip
2025-06-21 Added the board
    needs some work
2025-06-21 Moved stuff into folders
2025-06-21 Added Holder
2025-06-21 Small changes
2025-06-21 added fintester
2025-06-22 fixed
2025-06-26 Fixed CAD/Code location

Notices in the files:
parts and their libraries:
SparkFun-Electromechanical: Licensing: Creative Commons ShareAlike 4.0 International - https://creativecommons.org/licenses/by-sa/4.0
COPYRIGHT: Copyright (C) 2025 Ultra Librarian. All rights reserved.
